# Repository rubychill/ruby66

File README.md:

# ruby66
66 key split ergo keyboard, based on the lily58 and redox

# design considerations
- same key stagger layout as the lily58
- angled thumb button placed under the 5/6 columns a la redox
- bottom row extended back towards the pinky corner

# building
design can be built from scratch using the ergogen config file. the pcb uses [ceoloide's footprints](https://github.com/ceoloide/ergogen-footprints).

provided gerber files can be used to purchase the PCB from your manufacturer of choice

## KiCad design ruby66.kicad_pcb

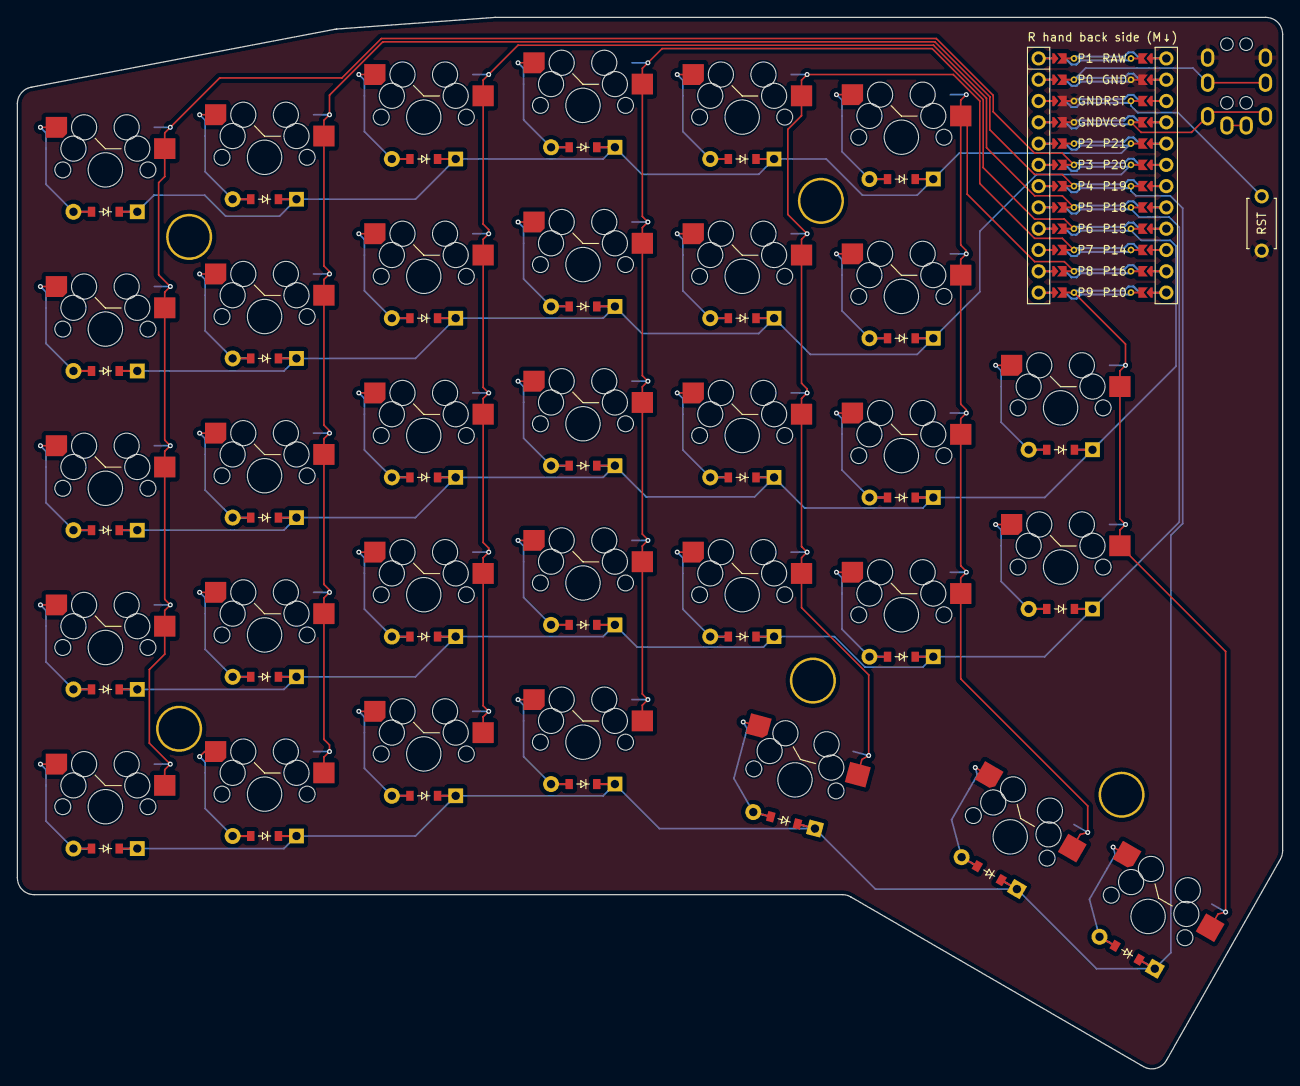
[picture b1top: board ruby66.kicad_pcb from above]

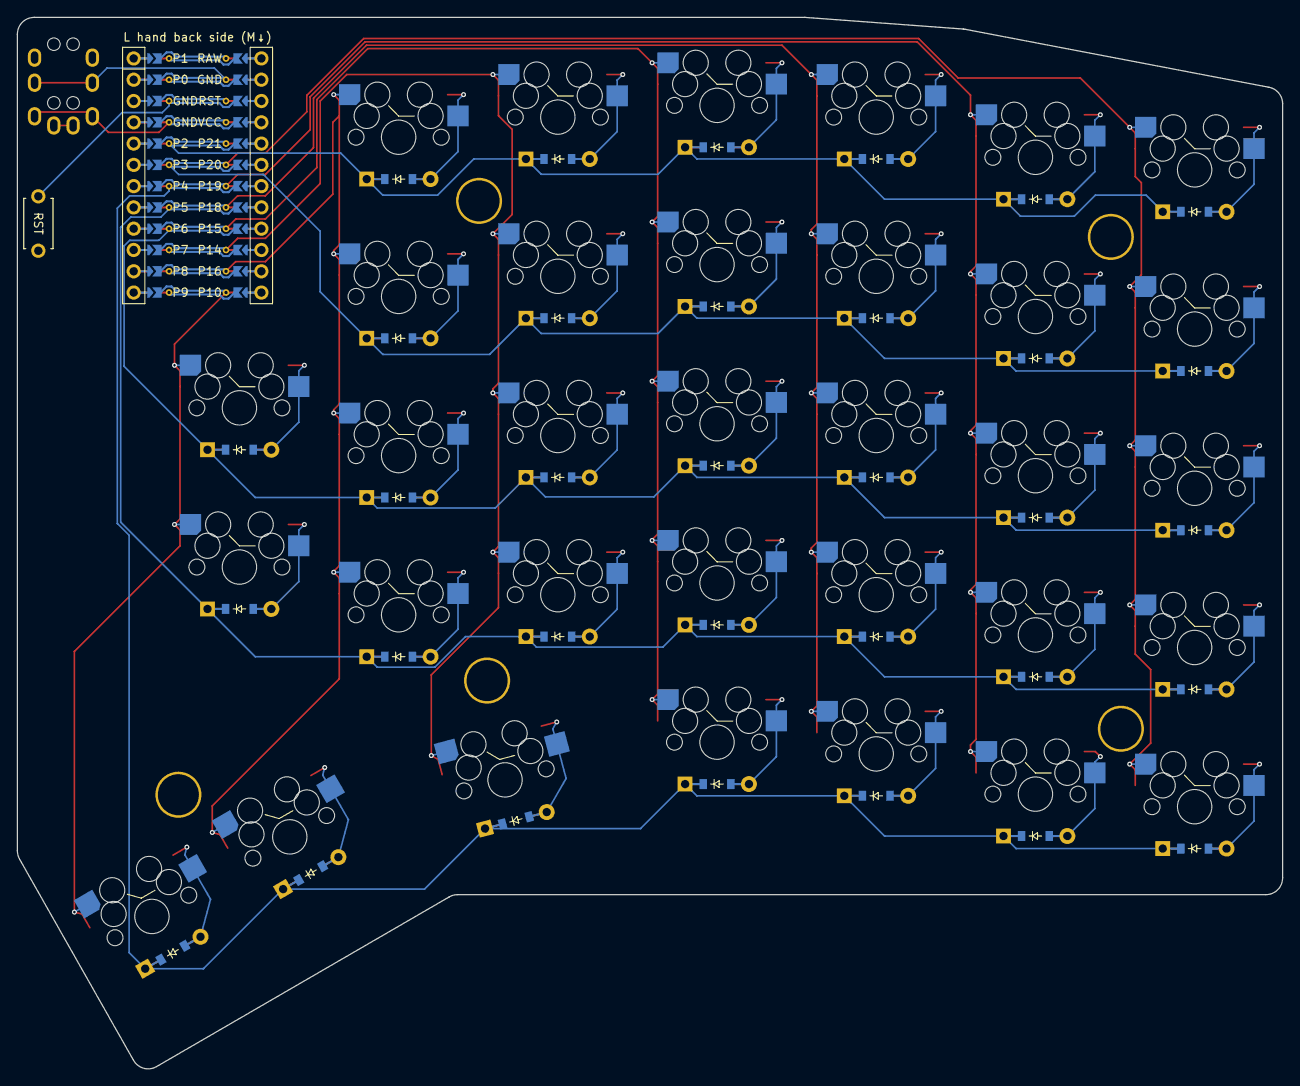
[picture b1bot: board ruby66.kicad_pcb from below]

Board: 2 copper layers, 151.0 x 125.5 mm, 74 parts (33 on the bottom side), 49 nets.

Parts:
D1, D2, D3, D4, D5, D6, D7, D8, D9, D10, D11, D12, D13, D14, D15, D16, D17, D18, D19, D20, D21, D22, D23, D24, D25, D26, D27, D28, D29, D30, D31, D32, D33: diode_tht_sod123
H1, H2, H3, H4, H5: mounting_hole_plated
MCU1: mcu_nice_nano
RST1: reset_switch_tht_top
S1, S2, S3, S4, S5, S6, S7, S8, S9, S10, S11, S12, S13, S14, S15, S16, S17, S18, S19, S20, S21, S22, S23, S24, S25, S26, S27, S28, S29, S30, S31, S32, S33: switch_mx
TRRS1: trrs_pj320a (reversible)

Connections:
GND: MCU1.102, MCU1.121, MCU1.122, RST1.2, TRRS1.2
P0: MCU1.123, TRRS1.3
P3: MCU1.119, S1.1, S1.2, S2.1, S2.2, S3.1, S3.2, S4.1, S4.2, S5.1, S5.2
P4: MCU1.118, S6.1, S6.2, S7.1, S7.2, S8.1, S8.2, S9.1, S9.2, S10.1, S10.2
P5: MCU1.117, S11.1, S11.2, S12.1, S12.2, S13.1, S13.2, S14.1, S14.2, S15.1, S15.2
P6: MCU1.116, S16.1, S16.2, S17.1, S17.2, S18.1, S18.2, S19.1, S19.2, S20.1, S20.2
P7: MCU1.115, S21.1, S21.2, S22.1, S22.2, S23.1, S23.2, S24.1, S24.2, S31.1, S31.2
P8: MCU1.114, S25.1, S25.2, S26.1, S26.2, S27.1, S27.2, S28.1, S28.2, S32.1, S32.2
P9: MCU1.113, S29.1, S29.2, S30.1, S30.2, S33.1, S33.2
P15: D3.1, D8.1, D13.1, D18.1, D22.1, D26.1, D30.1, MCU1.109
P18: D2.1, D7.1, D12.1, D17.1, D21.1, D25.1, D29.1, MCU1.108
P19: D1.1, D6.1, D11.1, D16.1, D31.1, D32.1, D33.1, MCU1.107
P20: D4.1, D9.1, D14.1, D19.1, D23.1, D27.1, MCU1.106
P21: D5.1, D10.1, D15.1, D20.1, D24.1, D28.1, MCU1.105
RST: MCU1.103, RST1.1
VCC: MCU1.104, TRRS1.4
col0_row0: D1.2, S1.1, S1.2
col0_row1: D2.2, S2.1, S2.2
col0_row2: D3.2, S3.1, S3.2
col0_row3: D4.2, S4.1, S4.2
col0_row4: D5.2, S5.1, S5.2
col1_row0: D6.2, S6.1, S6.2
col1_row1: D7.2, S7.1, S7.2
col1_row2: D8.2, S8.1, S8.2
col1_row3: D9.2, S9.1, S9.2
col1_row4: D10.2, S10.1, S10.2
col2_row0: D11.2, S11.1, S11.2
col2_row1: D12.2, S12.1, S12.2
col2_row2: D13.2, S13.1, S13.2
col2_row3: D14.2, S14.1, S14.2
col2_row4: D15.2, S15.1, S15.2
col3_row0: D16.2, S16.1, S16.2
col3_row1: D17.2, S17.1, S17.2
col3_row2: D18.2, S18.1, S18.2
col3_row3: D19.2, S19.1, S19.2
col3_row4: D20.2, S20.1, S20.2
col4_row1: D21.2, S21.1, S21.2
col4_row2: D22.2, S22.1, S22.2
col4_row3: D23.2, S23.1, S23.2
col4_row4: D24.2, S24.1, S24.2
col5_row1: D25.2, S25.1, S25.2
col5_row2: D26.2, S26.1, S26.2
col5_row3: D27.2, S27.1, S27.2
col5_row4: D28.2, S28.1, S28.2
col6_row1: D29.2, S29.1, S29.2
col6_row2: D30.2, S30.1, S30.2
inner_lower: D32.2, S32.1, S32.2
outer_lower: D33.2, S33.1, S33.2
space_col_space_row: D31.2, S31.1, S31.2
